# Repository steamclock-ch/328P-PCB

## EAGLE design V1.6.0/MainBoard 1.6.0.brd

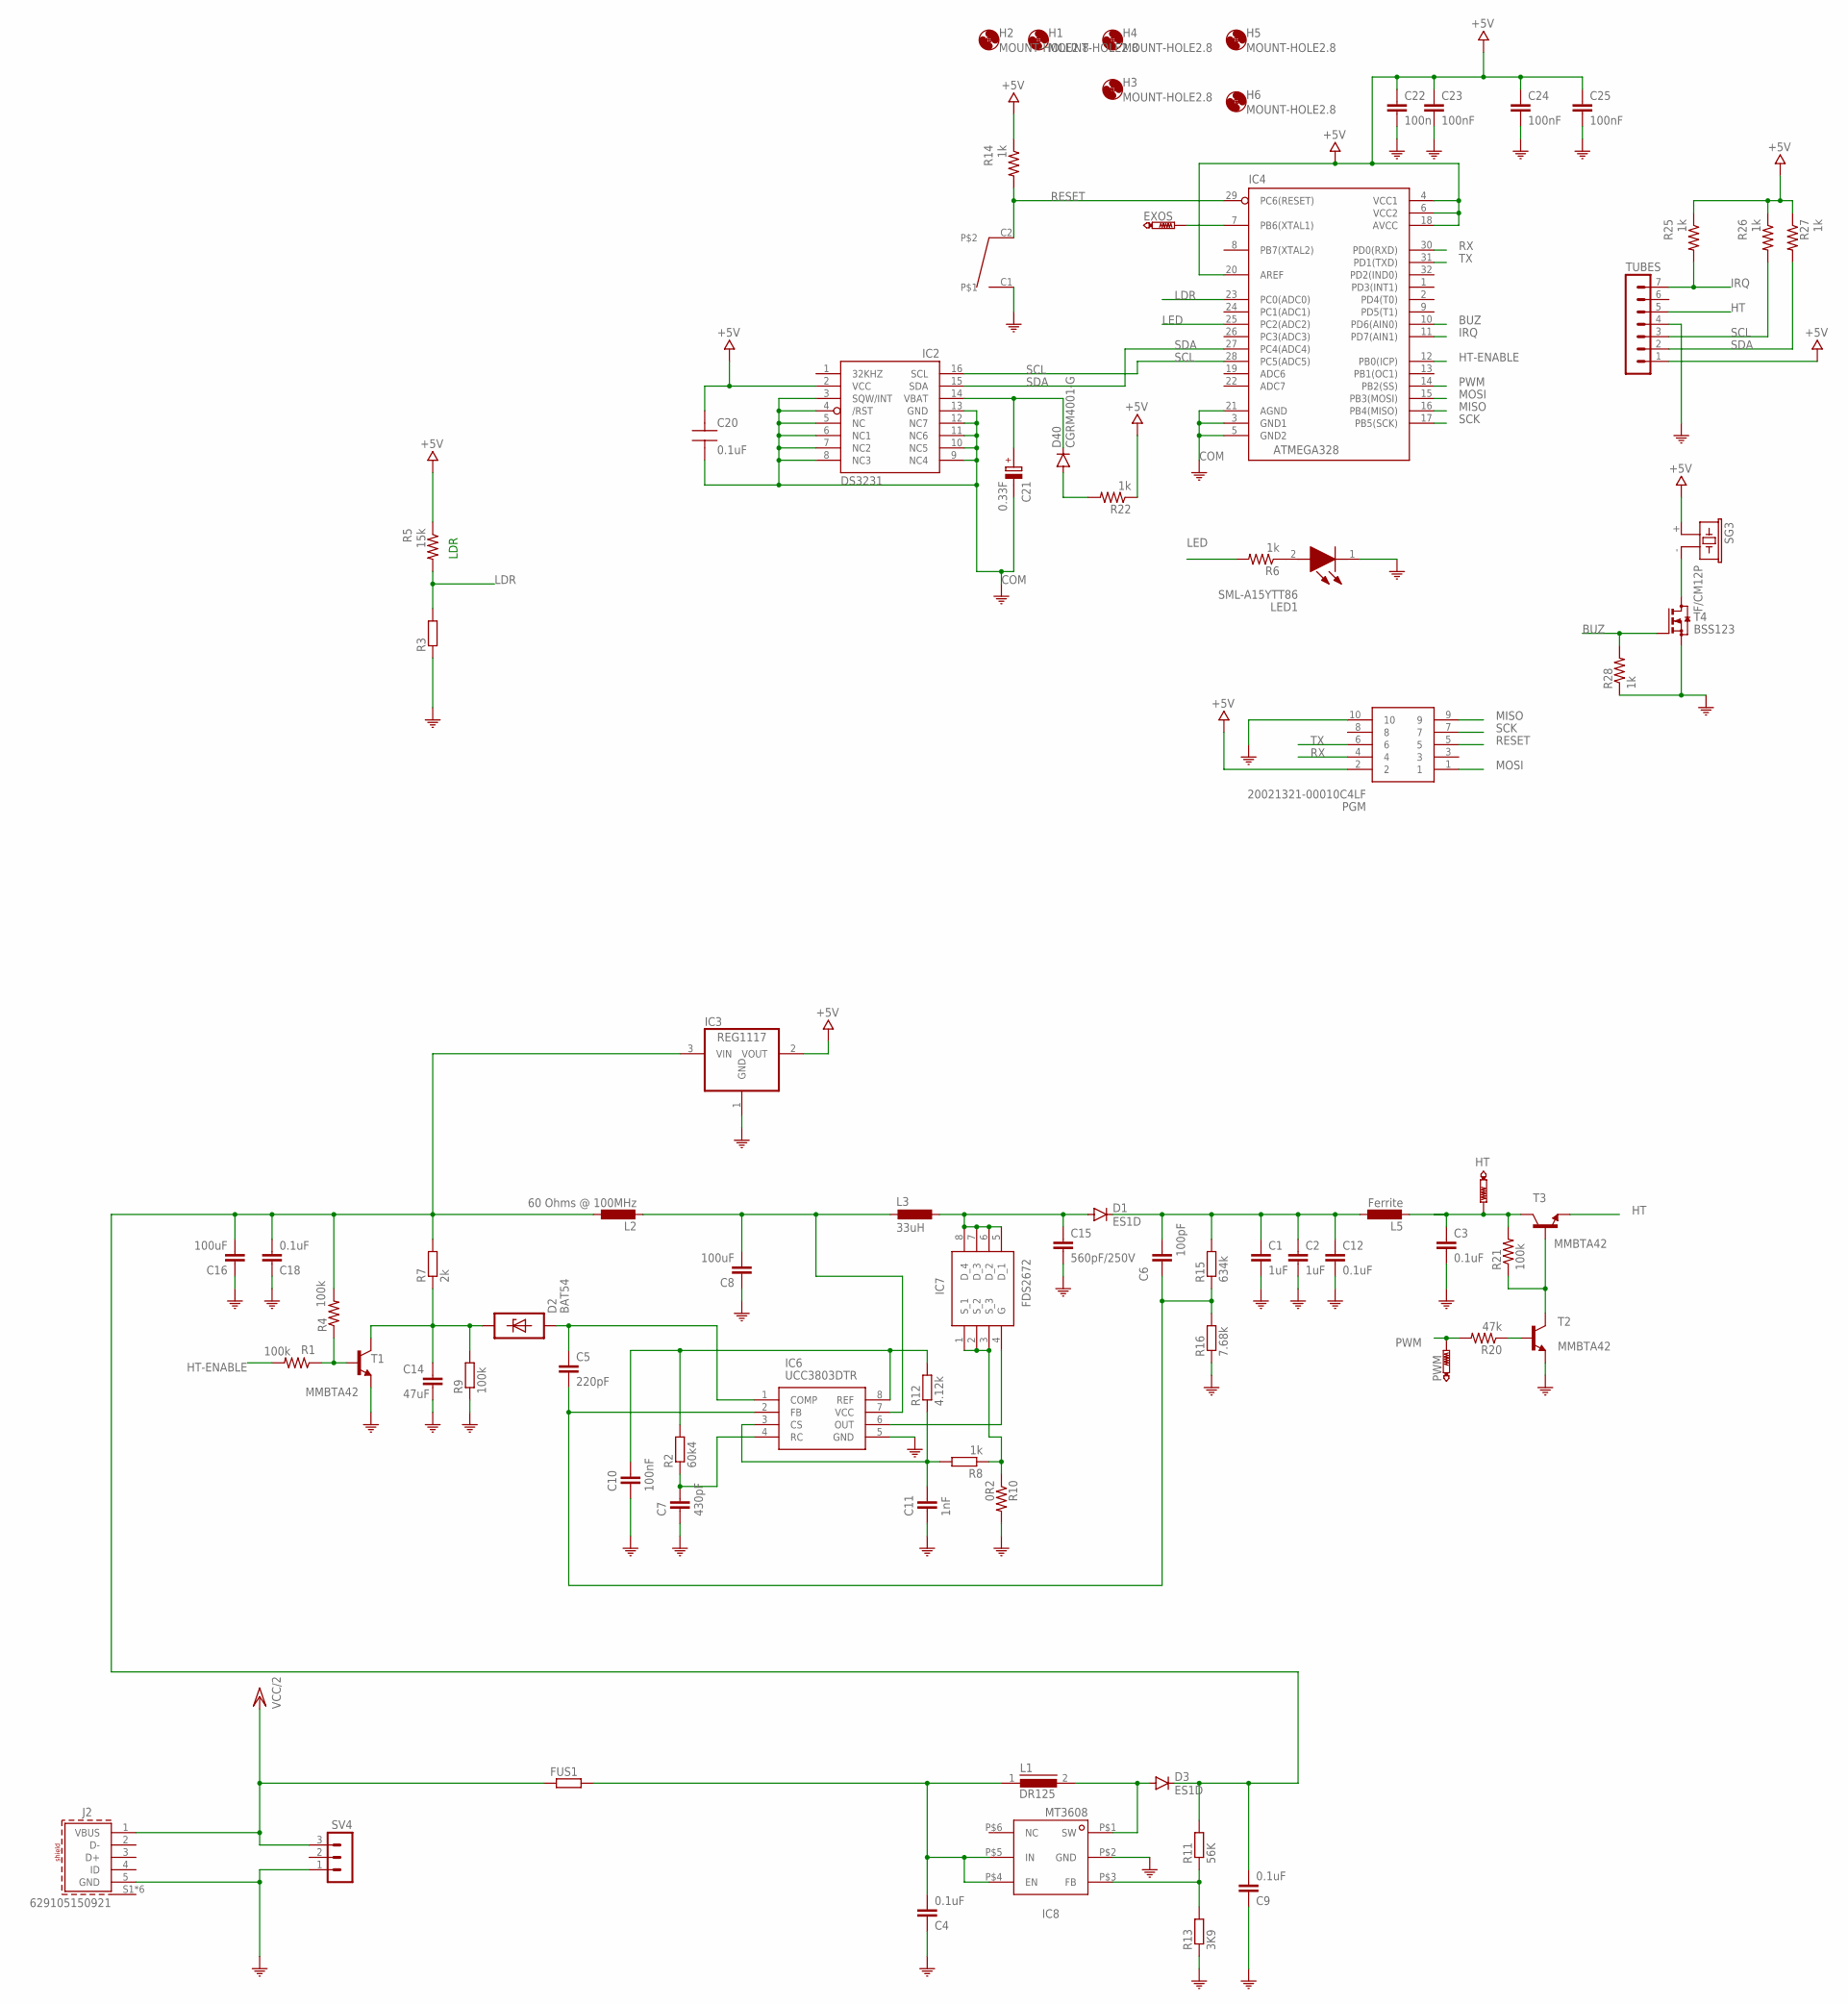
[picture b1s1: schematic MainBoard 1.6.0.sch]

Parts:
C1, C2: 1uF; C1812K; MOUSER 810-CGA8P3X7T2E105MA
C3, C12: 0.1uF; C1808; MOUSER 581-1808PC104KAT1A
C4: 0.1uF; C1206; MOUSER 963-LMF105B7104KVHF
C5: 220pF; C0402; MOUSER 963-LMK042B7221KC-W
C6: 100pF; C0805; MOUSER 81-GCM21A5C2E101JX1D
C7: 430pF; C0805; MOUSER 581-08055A431JAT4A
C8, C16: 100uF; C1210; MOUSER 963-EMK325ABJ107MM-P
C9: 0.1uF; C1206K; MOUSER 963-LMF105B7104KVHF
C10: 100nF; C0805; MOUSER 963-EMF212B7104KGHT
C11: 1nF; C0805; MOUSER 80-C0805C182G4HACTU
C14: 47uF; C1210; MOUSER 963-EMK325BJ476MM-P
C15: 560pF/250V; C0603; MOUSER 80-C0603C561JAG
C18: 0.1uF; C0402; MOUSER 963-LMF105B7104KVHF
C20: 0.1uF; CAP0805-NP
C21: 0.33F; ELNA21.5X8.0; MOUSER 555-DBN-5R5D334T
C22: 100n; C0603
C23, C24, C25: 100nF; C0603
D1, D3: ES1D; SMB; MOUSER 512-ES1DF
D2: BAT54; SOD323; MOUSER 621-BAT54WS-F
D40: CGRM4001-G; SOD-123_MINI-SMA; MOUSER 863-NSR0320MW2T1G
EXOS: PTR1TP09R; TP09R
FUS1: R-EU_R6332; R6332; MOUSER 530-0ZCG0150AF2C
H1, H2, H3, H4, H5, H6: MOUNT-HOLE2.8; 2,8
HT: PTR1TP09R; TP09R
IC2: DS3231/SO; SO16W; MOUSER 700-DS3231SN#
IC3: REG1117; SOT223
IC4: ATMEGA328; QFP032
IC6: UCC3803DTR; SOIC127P600X175-8N; MOUSER 595-UCC3803D
IC7: FDS2672; SOIC127P600X175-8N; MOUSER 512-FDS2672
IC8: MT3608SOT23-6; SOT23-6
J2: 629105150921; MOUSER 710-629105150921
L1: DR125
L2: 60 Ohms @ 100MHz; L2012C; MOUSER 963-BKP2125HS600-T
L3: 33uH; MSS7341; MOUSER 710-784770330
L5: Ferrite; L2012C; MOUSER 963-BKP2125HS600-T
LED1: SML-A15YTT86; SMLA15YTT86; MOUSER 755-SML-A15YTT86
PGM: 20021321-00010C4LF; 2002132100010C4LF
PWM: PTR1TP09R; TP09R
R1, R4, R9, R21: 100k; R0805
R2: 60k4; R0805; MOUSER 603-RT0805FRE0760K4L
R3: R-EU_0204/2V; 0204V
R5: 15k; M2012
R6, R14, R22, R25, R26, R27, R28: 1k; M2012
R7: 2k; R0805; MOUSER 754-RR1220P-202D
R8: 1k; R0805
R10: 0R2; R2010; MOUSER 603-PE2010FKE070R1L
R11: 56K; R0805; MOUSER 71-CRCW0603-634K-E3
R12: 4.12k; R0805; MOUSER 660-RN732ATD4121F100
R13: 3K9; R0805; MOUSER 71-CRCW0603-634K-E3
R15: 634k; R0805; MOUSER 71-CRCW0603-634K-E3
R16: 7.68k; R0805; MOUSER 71-CRCW0805-7.68K-E3
R20: 47k; R0805
SG3: F/CM12P
SV4: MA03-1
T1, T2, T3: MMBTA42; SOT23
T4: BSS123; SOT23; MOUSER 726-BSS123NH6433
TUBES: MA07-1
U$5: D-VERTSW; FP-VERTSW; MOUSER 612-TL6190BUTTON

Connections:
+5V: C20.1, C22.1, C23.1, C24.1, C25.1, IC2.2 (VCC), IC3.2 (VOUT), IC4.4 (VCC1), IC4.6 (VCC2), IC4.18 (AVCC), IC4.20 (AREF), PGM.2, R5.1, R14.1, R22.1, R25.1, R26.1, R27.1, SG3.+ (1), TUBES.1
BATT: C21.+, D40.C, IC2.14 (VBAT)
BUZ: IC4.10 (PD6(AIN0)), R28.2, T4.1 (G)
COM: C1.2, C2.2, C3.2, C4.2, C7.2, C8.1, C9.2, C10.2, C11.2, C12.2, C14.2, C15.2, C16.1, C18.2, C20.2, C21.-, C22.2, C23.2, C24.2, C25.2, IC2.3 (SQW/INT), IC2.4 (/RST), IC2.5 (NC), IC2.6 (NC1), IC2.7 (NC2), IC2.8 (NC3), IC2.9 (NC4), IC2.10 (NC5), IC2.11 (NC6), IC2.12 (NC7), IC2.13 (GND), IC3.1 (GND), IC4.3 (GND1), IC4.5 (GND2), IC4.21 (AGND), IC6.5 (GND), IC8.P$2 (GND), J2.5 (GND), LED1.1 (K), PGM.10, R3.1, R9.1, R10.2, R13.1, R16.1, R28.1, SV4.1, T1.2 (E), T2.2 (E), T4.2 (S), TUBES.4, U$5.C1
CS: C11.1, IC6.3 (CS), R8.2, R12.1
FB: C5.2, C6.2, IC6.2 (FB), R15.1, R16.2
HT: T3.2 (E), TUBES.5
HT-ENABLE: IC4.12 (PB0(ICP)), R1.2
IRQ: IC4.11 (PD7(AIN1)), R25.2, TUBES.7
LDR: IC4.23 (PC0(ADC0)), R3.2, R5.2
LED: IC4.25 (PC2(ADC2)), R6.2
MISO: IC4.16 (PB4(MISO)), PGM.9
MOSI: IC4.15 (PB3(MOSI)), PGM.1
unnamed: LED1.2 (A), R6.1
unnamed: C4.1, FUS1.2, IC8.P$4 (EN), IC8.P$5 (IN), L1.1
unnamed: SG3.- (2), T4.3 (D)
unnamed: EXOS.TP, IC4.7 (PB6(XTAL1))
unnamed: C1.1, C2.1, C6.1, C12.1, D1.C, L5.1, R15.2
unnamed: R21.1, T2.3 (C), T3.1 (B)
unnamed: R1.1, R4.1, T1.1 (B)
unnamed: C14.1, D2.C (1), R7.1, R9.2, T1.3 (C)
unnamed: C5.1, D2.A (2), IC6.1 (COMP)
unnamed: IC8.P$3 (FB), R11.1, R13.2
unnamed: IC7.1 (S_1), IC7.2 (S_2), IC7.3 (S_3), R8.1, R10.1
unnamed: D3.A, IC8.P$1 (SW), L1.2
unnamed: C8.2, IC6.7 (VCC), L2.2, L3.1
unnamed: C15.1, D1.A, IC7.5 (D_1), IC7.6 (D_2), IC7.7 (D_3), IC7.8 (D_4), L3.2
unnamed: R20.1, T2.1 (B)
unnamed: D40.A, R22.2
OUT: IC6.6 (OUT), IC7.4 (G)
POSTFUSE: C9.1, C16.2, C18.1, D3.C, IC3.3 (VIN), L2.1, R4.2, R7.2, R11.2
PWM: IC4.14 (PB2(SS)), PWM.TP, R20.2
RAW_HT: C3.1, HT.TP, L5.2, R21.2, T3.3 (C)
RC: C7.1, IC6.4 (RC), R2.1
REF: C10.1, IC6.8 (REF), R2.2, R12.2
RESET: IC4.29 (PC6(RESET)), PGM.5, R14.2, U$5.C2
RX: IC4.30 (PD0(RXD)), PGM.4
SCK: IC4.17 (PB5(SCK)), PGM.7
SCL: IC2.16 (SCL), IC4.28 (PC5(ADC5)), R26.2, TUBES.3
SDA: IC2.15 (SDA), IC4.27 (PC4(ADC4)), R27.2, TUBES.2
TX: IC4.31 (PD1(TXD)), PGM.6
VCC/2: FUS1.1, J2.1 (VBUS), SV4.3

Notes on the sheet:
LDR

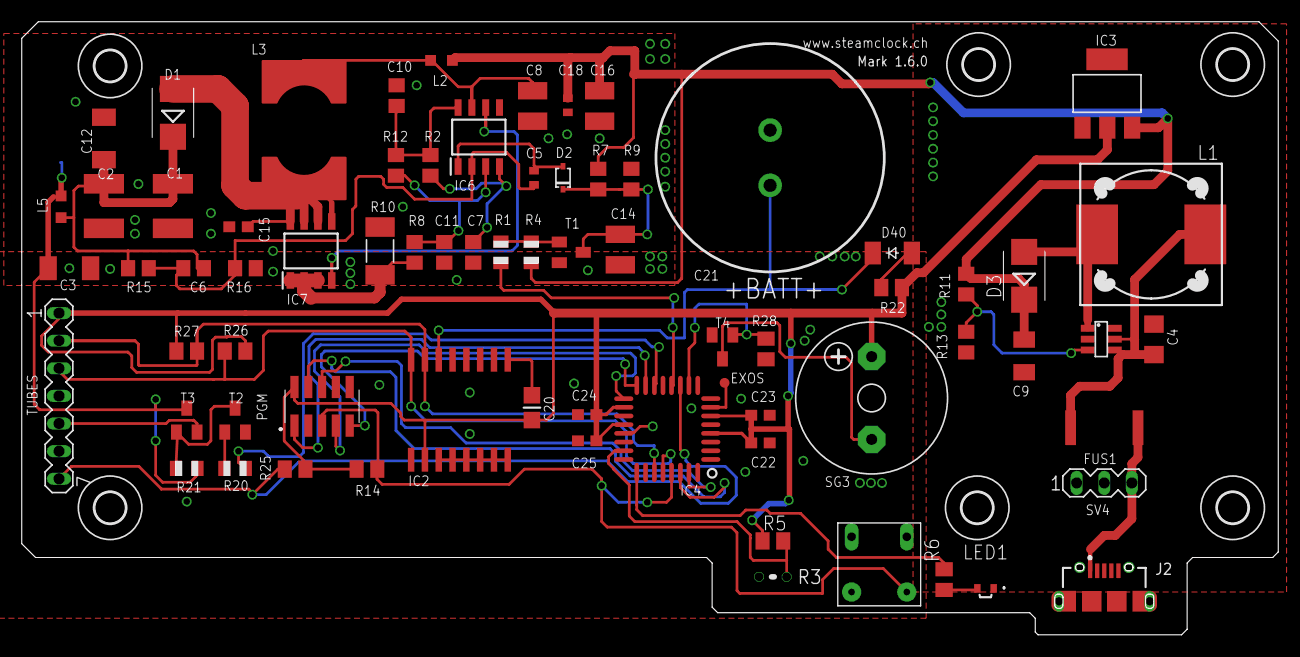
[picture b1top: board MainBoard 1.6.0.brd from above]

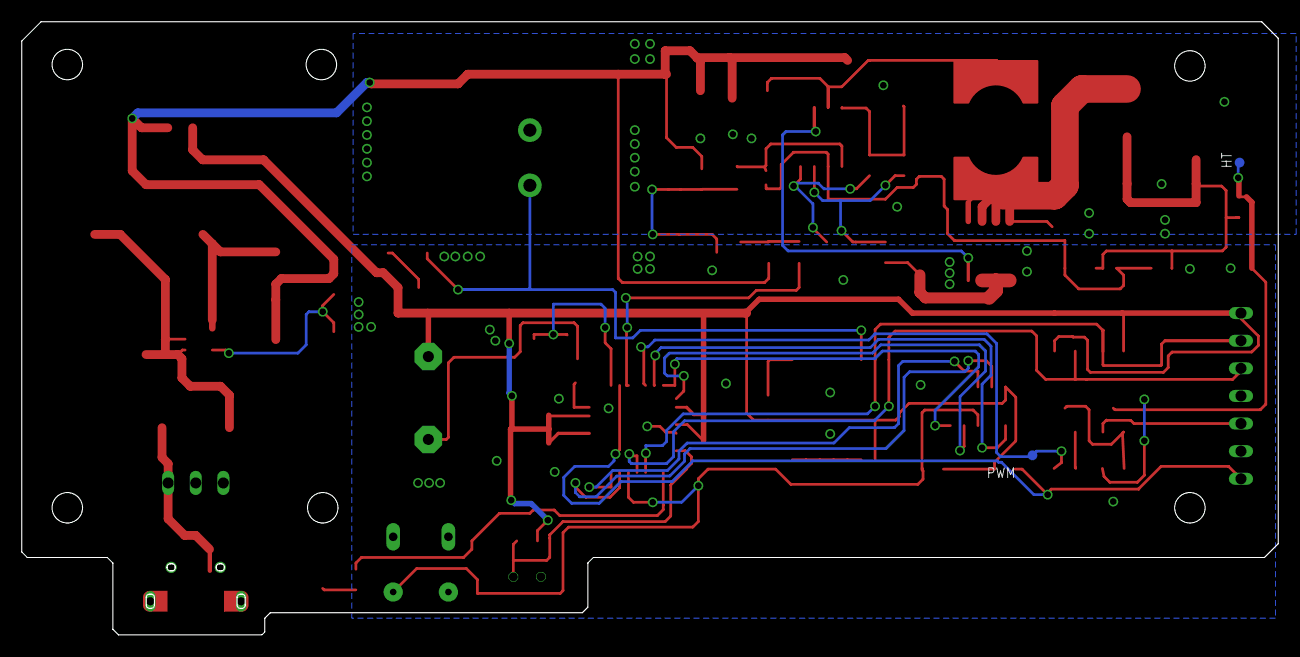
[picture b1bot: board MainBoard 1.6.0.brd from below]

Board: 2 copper layers, 115.5 x 56.3 mm, 80 parts (2 on the bottom side), 42 nets.

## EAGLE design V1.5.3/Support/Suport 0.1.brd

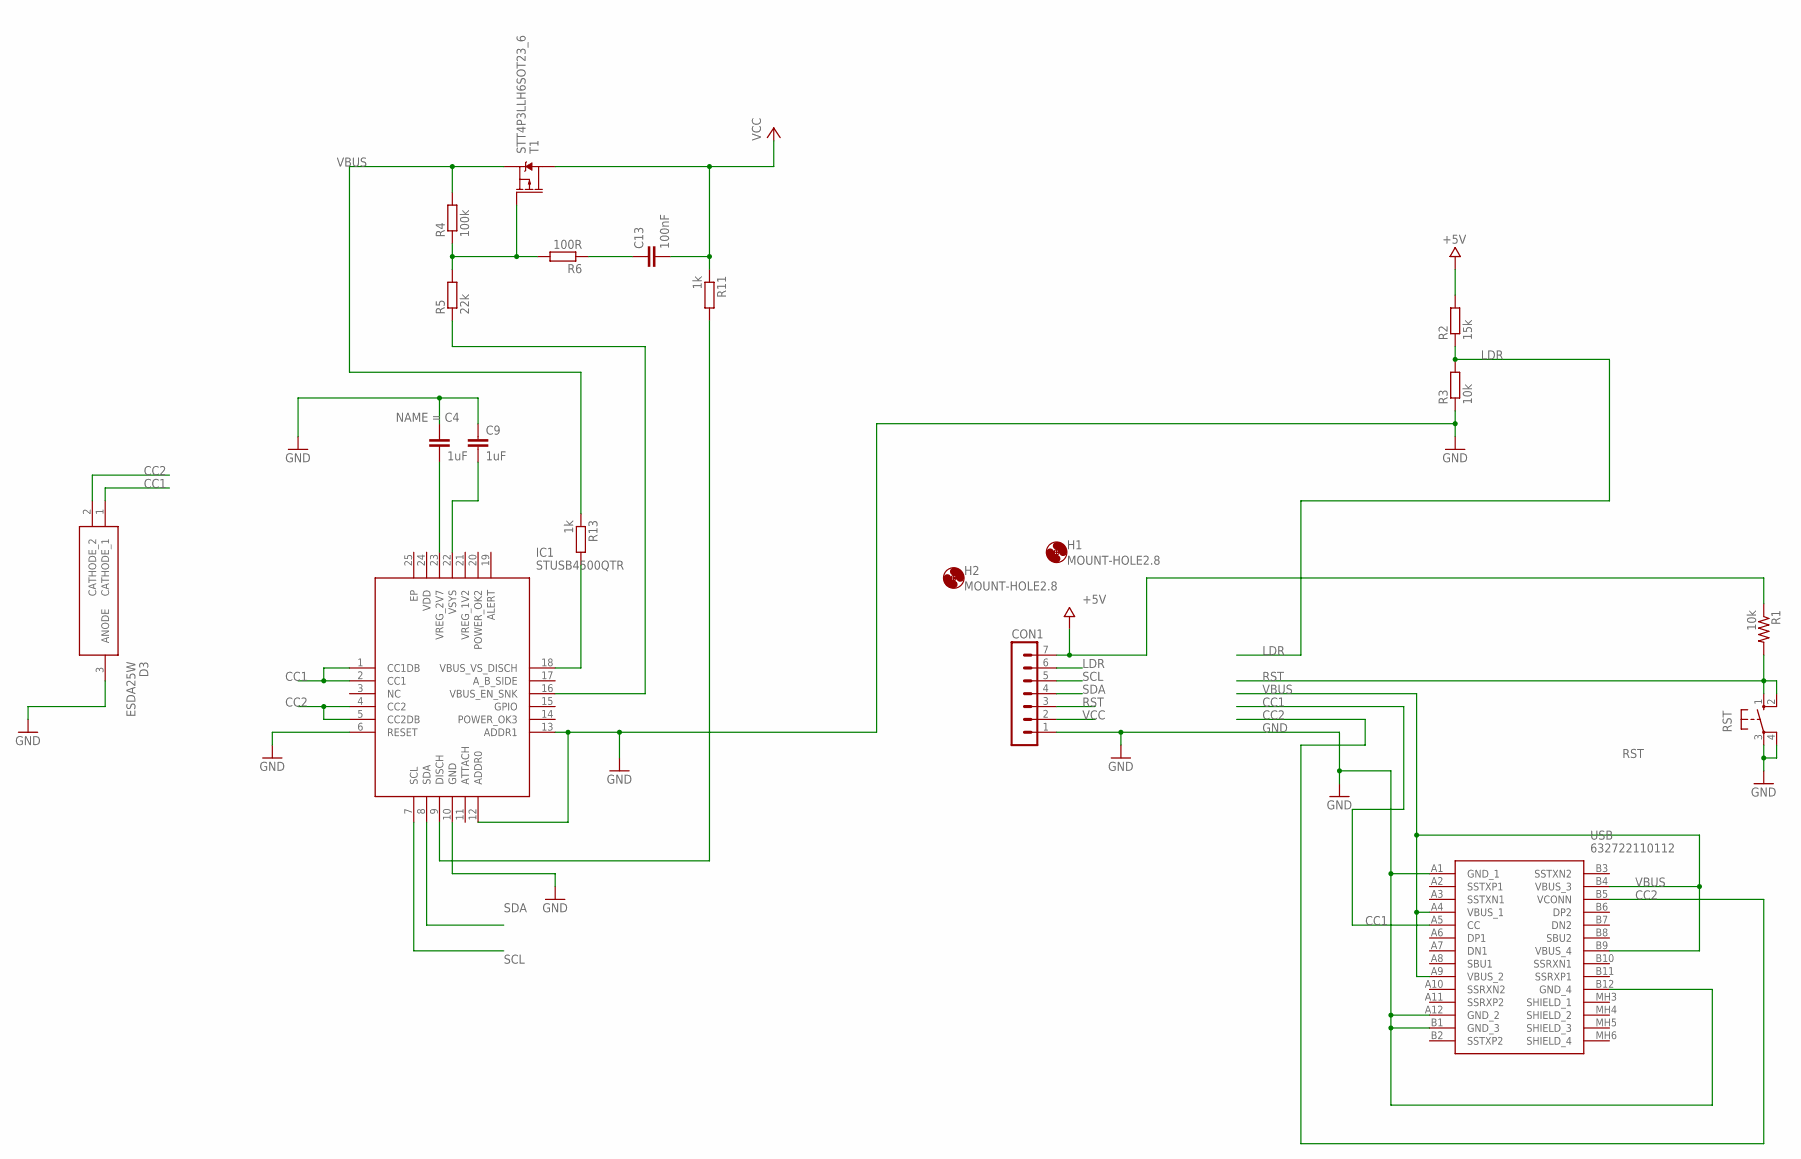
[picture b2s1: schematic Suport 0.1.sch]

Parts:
C4: 1uF; C0603; MOUSER_PART_NUMBER 81-GRM155R61E105KA2D
C9: 1uF; C0603
C13: 100nF; C0402; MOUSER_PART_NUMBER 710-885012205050
CON1: MA07-1
D3: ESDA25W; SOT65P210X110-3N
H1, H2: MOUNT-HOLE2.8; 2,8
IC1: STUSB4500QTR; QFN50P400X400X100-25N
R1, R3: 10k; M2012
R2: 15k; 0204V
R4: 100k; R0805
R5: 22k; R0805
R6: 100R; R0805
R11, R13: 1k; R0805
RST: 10-XX; B3F-10XX
T1: STT4P3LLH6SOT23_6; SOT23-6
USB: 632722110112

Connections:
+5V: CON1.7, R1.1, R2.2
CC1: D3.1 (CATHODE_1), IC1.1 (CC1DB), IC1.2 (CC1), USB.A5 (CC)
CC2: D3.2 (CATHODE_2), IC1.4 (CC2), IC1.5 (CC2DB), USB.B5 (VCONN)
GND: C4.1, C9.1, CON1.1, D3.3 (ANODE), IC1.6 (RESET), IC1.10 (GND), IC1.12 (ADDR0), IC1.13 (ADDR1), R3.1, RST.3, RST.4 (P1), USB.A1 (GND_1), USB.A12 (GND_2), USB.B1 (GND_3), USB.B12 (GND_4)
LDR: CON1.6, R2.1, R3.2
unnamed: C4.2, IC1.23 (VREG_2V7)
unnamed: C9.2, IC1.22 (VSYS)
unnamed: R4.1, R5.2, R6.2, T1.3 (G)
unnamed: C13.1, R6.1
unnamed: IC1.16 (VBUS_EN_SNK), R5.1
unnamed: IC1.9 (DISCH), R11.2
unnamed: IC1.18 (VBUS_VS_DISCH), R13.2
RST: CON1.3, R1.2, RST.1 (S), RST.2 (S1)
SCL: CON1.5, IC1.7 (SCL)
SDA: CON1.4, IC1.8 (SDA)
VBUS: R4.2, R13.1, T1.4 (S), USB.A4 (VBUS_1), USB.A9 (VBUS_2), USB.B4 (VBUS_3), USB.B9 (VBUS_4)
VCC: C13.2, CON1.2, R11.1, T1.1 (D), T1.2 (D), T1.5 (D), T1.6 (D)

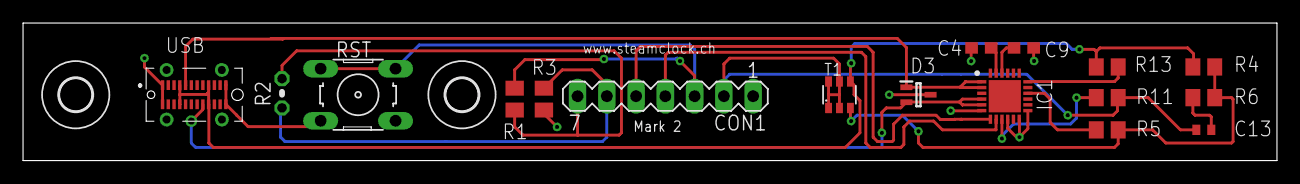
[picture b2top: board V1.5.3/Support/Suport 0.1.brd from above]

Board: 2 copper layers, 108.8 x 11.9 mm, 19 parts (0 on the bottom side), 17 nets.

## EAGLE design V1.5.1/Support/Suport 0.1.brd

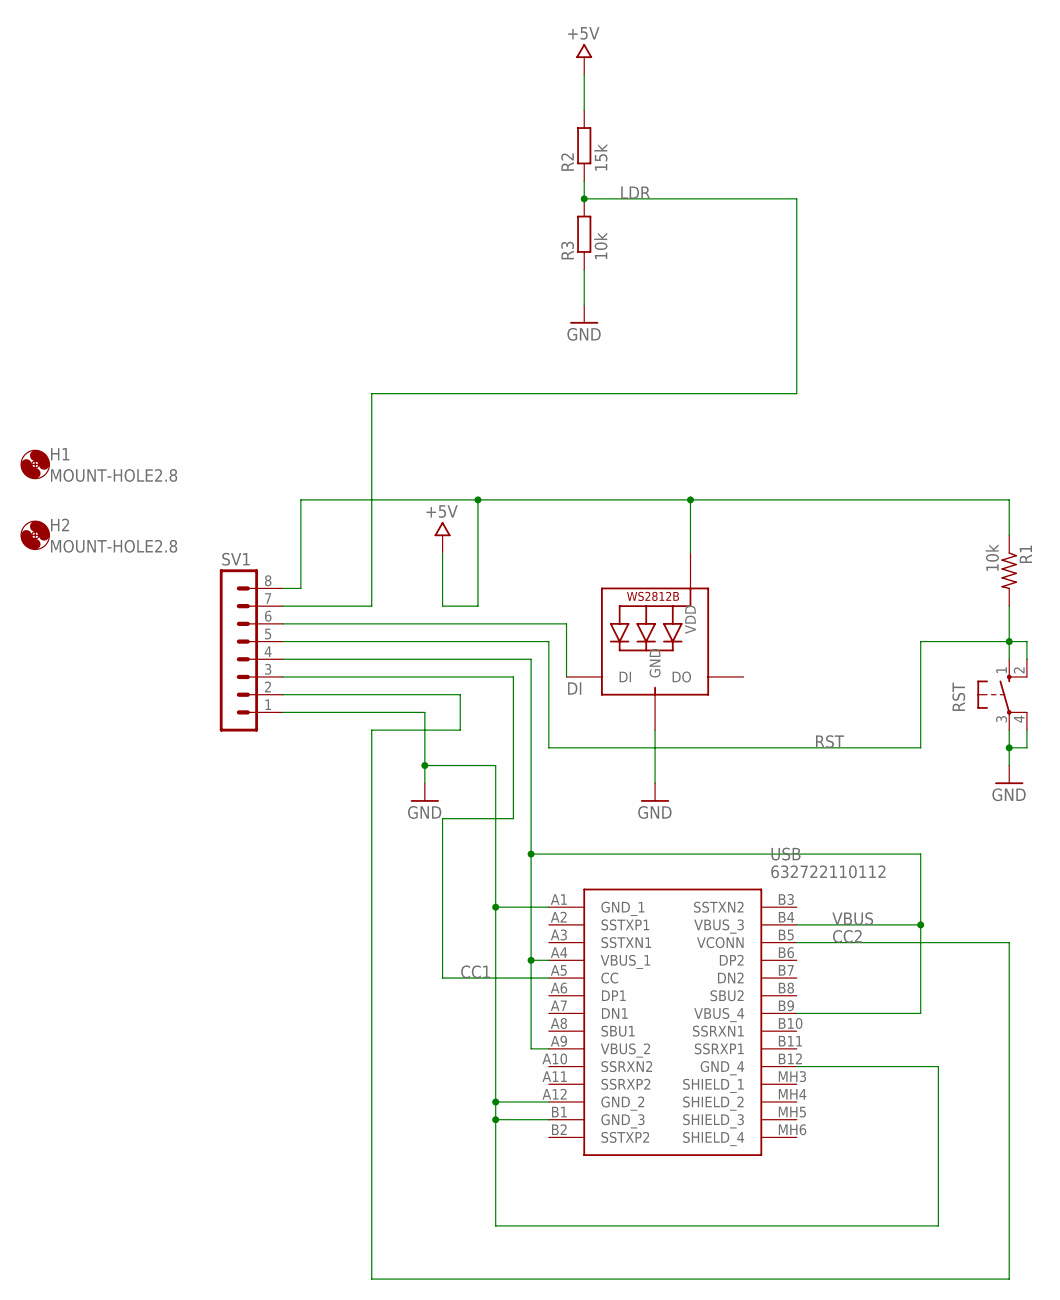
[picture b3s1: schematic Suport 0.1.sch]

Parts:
H1, H2: MOUNT-HOLE2.8; 2,8
LED1: WS2812B3535; LED3535
R1, R3: 10k; M2012
R2: 15k; 0204V
RST: 10-XX; B3F-10XX
SV1: MA08-1
USB: 632722110112

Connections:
+5V: LED1.2 (VDD), R1.1, R2.2, SV1.8
CC1: SV1.3, USB.A5 (CC)
CC2: SV1.2, USB.B5 (VCONN)
DI: LED1.1 (DI), SV1.6
GND: LED1.4 (GND), R3.1, RST.3, RST.4 (P1), SV1.1, USB.A1 (GND_1), USB.A12 (GND_2), USB.B1 (GND_3), USB.B12 (GND_4)
LDR: R2.1, R3.2, SV1.7
RST: R1.2, RST.1 (S), RST.2 (S1), SV1.5
VBUS: SV1.4, USB.A4 (VBUS_1), USB.A9 (VBUS_2), USB.B4 (VBUS_3), USB.B9 (VBUS_4)

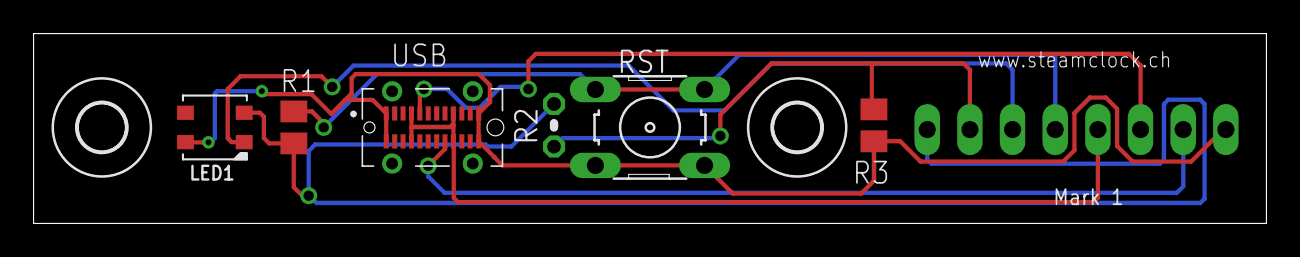
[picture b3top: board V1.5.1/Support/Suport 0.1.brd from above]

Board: 2 copper layers, 73.4 x 11.3 mm, 9 parts (1 on the bottom side), 8 nets.

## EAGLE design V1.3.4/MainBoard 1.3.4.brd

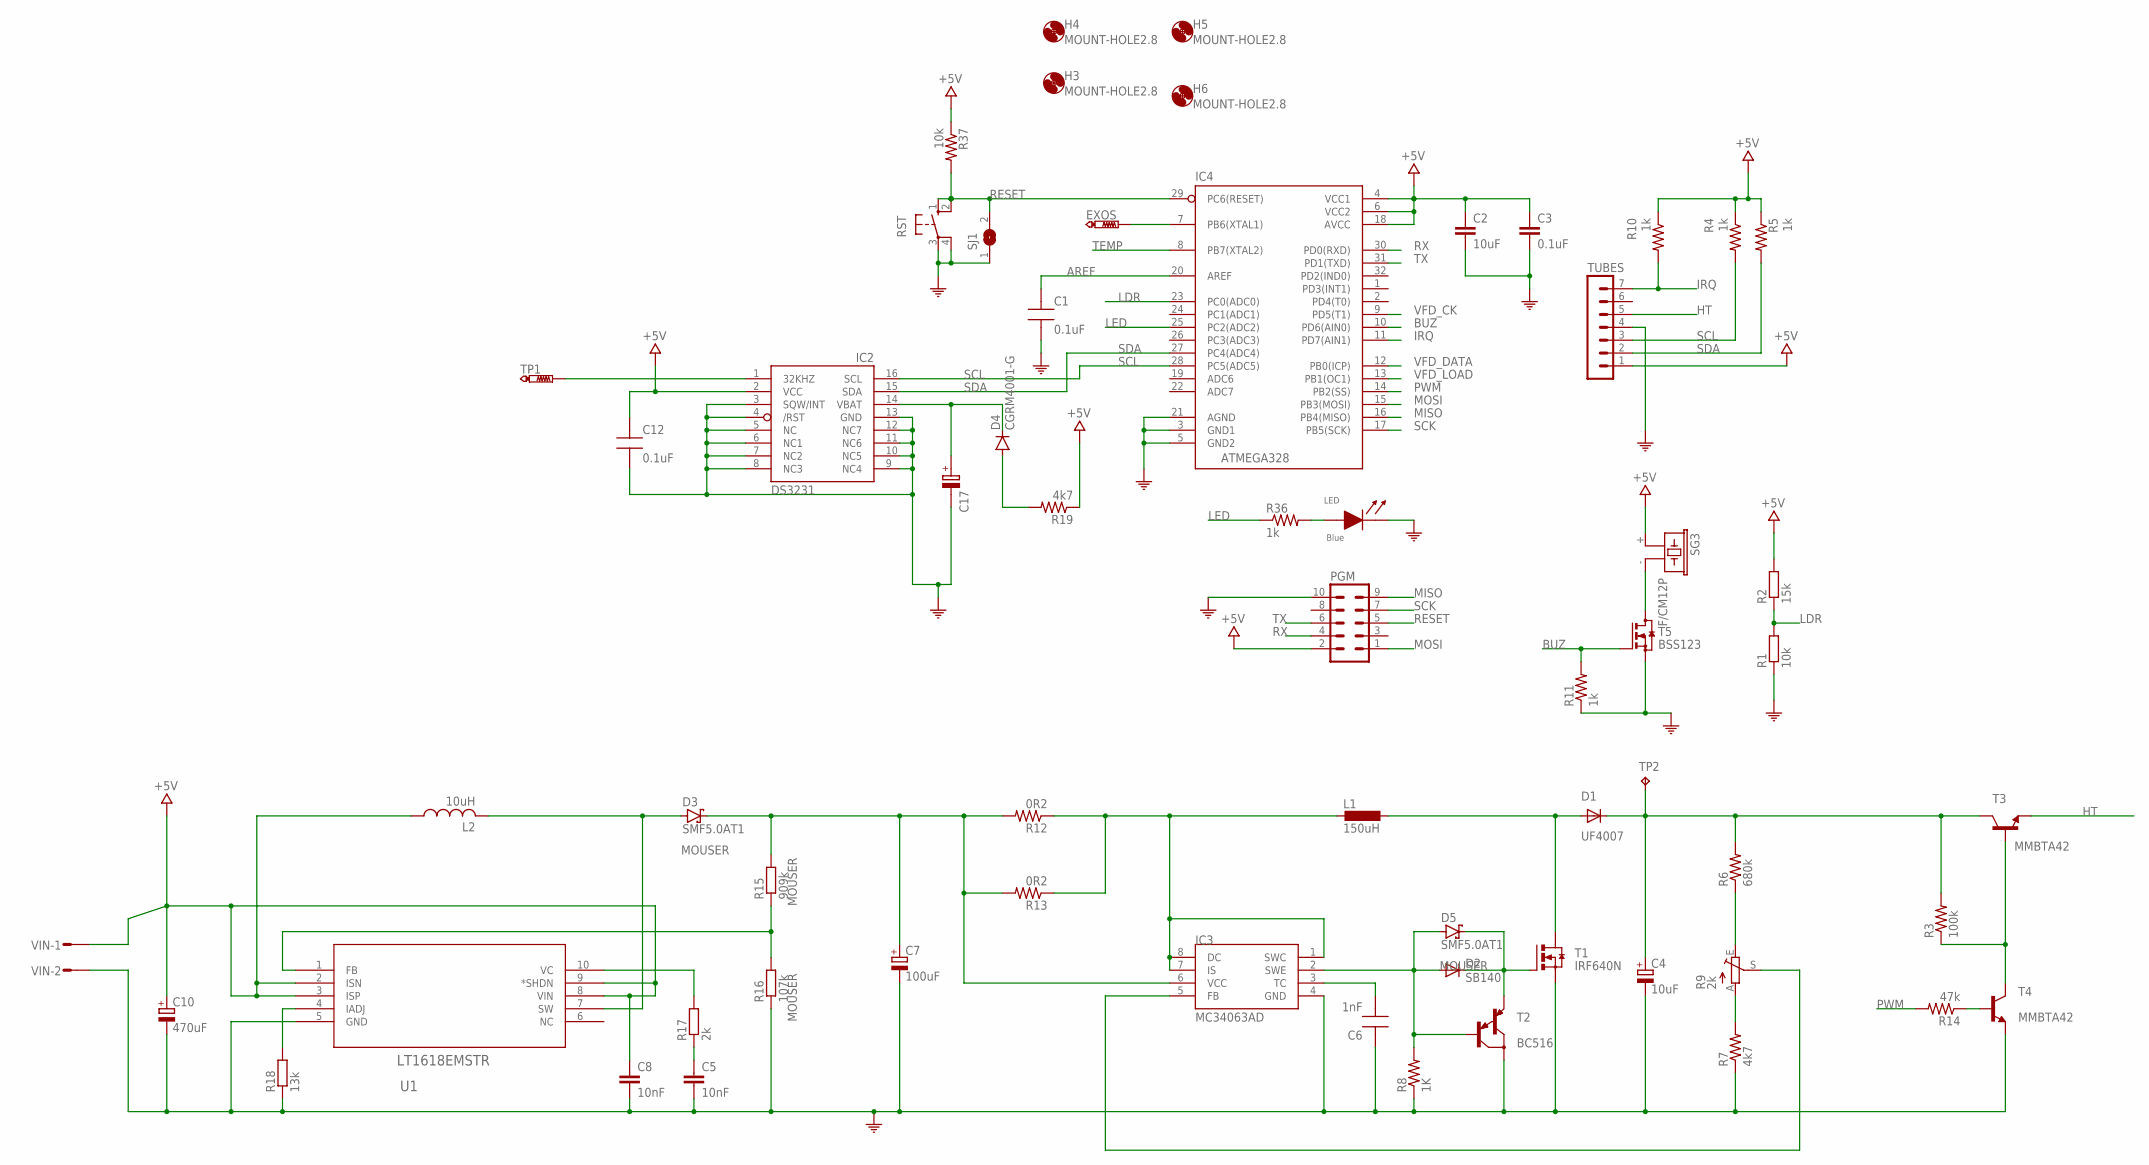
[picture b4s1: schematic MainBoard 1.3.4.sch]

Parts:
C1, C12: 0.1uF; CAP0805-NP
C2: 10uF; C0603; MOUSER 791-0603X106K100CT
C3: 0.1uF; C0402K; MOUSER 963-JMK042BJ104KC-W
C4: 10uF; E3,5-10
C5, C8: 10nF; C0805
C6: 1nF; CAP0805-NP
C7: 100uF; E2,5-6E
C10: 470uF; 153CLV-0810; MOUSER 710-865080253012
C17: AHG-35/100-RADIAL; ELNA21.5X8.0; MOUSER 555-DB-5R5D474T
D1: UF4007; F126-10
D2: SB140; DO07
D3, D5: SMF5.0AT1; SOD123FL; MOUSER 863-MBR0520LT1G
D4: CGRM4001-G; SOD-123_MINI-SMA; MOUSER 863-NSR0320MW2T1G
EXOS: PTR1TP09R; TP09R
H3, H4, H5, H6: MOUNT-HOLE2.8; 2,8
IC2: DS3231/SO; SO16W
IC3: MC34063AD; SOIC8
IC4: ATMEGA328; QFP032
L1: 150uH; DO3316P
L2: 10uH; L5650M; MOUSER 851-CR43NP-100MC
LED: Blue; LED0805
PGM: MA05-2
R1, R37: 10k; M2012
R2: 15k; 0204V
R3: 100k; R2012
R4, R5, R10, R11, R36: 1k; M2012
R6: 680k; R2012
R7: 4k7; R2012
R8: 1K; R2012
R9: 2k; B25P
R12, R13: 0R2; R2010
R14: 47k; R2012
R15: 909k; R0805; MOUSER 754-RR1220P-9093D-M
R16: 107k; R0805; MOUSER RR0816P-1073-D-04D
R17: 2k; R0805
R18: 13k; R0805
R19: 4k7; M2012
RST: 10-XX; B3F-10XX
SG3: F/CM12P
SJ1: SJW
T1: IRF640N; D2PACK
T2: BC516; TO92
T3, T4: MMBTA42; SOT23
T5: BSS123; SOT23
TP1: PTR1TP09R; TP09R
TP2: TPTP12R; TP12R
TUBES: MA07-1
U1: LT1618EMSTR; MSOP-10_MS; MOUSER 584-LT1618EMS#PBF
VIN: M02S; 02P

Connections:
+5V: C2.1, C3.1, C8.1, C10.+, C12.1, IC2.2 (VCC), IC4.4 (VCC1), IC4.6 (VCC2), IC4.18 (AVCC), L2.1, PGM.2, R2.2, R4.1, R5.1, R10.1, R19.1, R37.1, SG3.+ (1), TUBES.1, U1.2 (ISN), U1.3 (ISP), U1.8 (VIN), U1.9 (*SHDN), VIN.1
AREF: C1.1, IC4.20 (AREF)
BATT: C17.+, D4.C, IC2.14 (VBAT)
BUZ: IC4.10 (PD6(AIN0)), R11.2, T5.1 (G)
GND: C1.2, C2.2, C3.2, C4.-, C5.2, C6.1, C7.-, C8.2, C10.-, C12.2, C17.-, IC2.3 (SQW/INT), IC2.4 (/RST), IC2.5 (NC), IC2.6 (NC1), IC2.7 (NC2), IC2.8 (NC3), IC2.9 (NC4), IC2.10 (NC5), IC2.11 (NC6), IC2.12 (NC7), IC2.13 (GND), IC3.4 (GND), IC4.3 (GND1), IC4.5 (GND2), IC4.21 (AGND), LED.1 (CA), PGM.10, R1.1, R7.1, R8.1, R11.1, R16.1, R18.1, RST.3, RST.4 (P1), SJ1.1, T1.3 (S), T2.3 (C), T4.2 (E), T5.2 (S), TUBES.4, U1.5 (GND), VIN.2
HT: T3.2 (E), TUBES.5
IRQ: IC4.11 (PD7(AIN1)), R10.2, TUBES.7
LDR: IC4.23 (PC0(ADC0)), R1.2, R2.1
LED: IC4.25 (PC2(ADC2)), R36.1
MISO: IC4.16 (PB4(MISO)), PGM.9
MOSI: IC4.15 (PB3(MOSI)), PGM.1
unnamed: IC2.1 (32KHZ), TP1.TP
unnamed: D1.A, L1.2, T1.2 (D)
unnamed: SG3.- (2), T5.3 (D)
unnamed: EXOS.TP, IC4.7 (PB6(XTAL1))
unnamed: C6.2, IC3.3 (TC)
unnamed: R3.1, T3.1 (B), T4.3 (C)
unnamed: R7.2, R9.A
unnamed: D2.A, D5.A, IC3.2 (SWE), R8.2, T2.2 (B)
unnamed: R6.1, R9.E
unnamed: D3.A, L2.2, U1.7 (SW)
unnamed: R18.2, U1.4 (IADJ)
unnamed: LED.2 (AN), R36.2
unnamed: IC3.5 (FB), R9.S
unnamed: IC3.1 (SWC), IC3.7 (IS), IC3.8 (DC), L1.1, R12.1, R13.1
unnamed: R17.2, U1.10 (VC)
unnamed: R14.1, T4.1 (B)
unnamed: D2.C, D5.C, T1.1 (G), T2.1 (E)
unnamed: C5.1, R17.1
unnamed: D4.A, R19.2
unnamed: R15.1, R16.2, U1.1 (FB)
PWM: IC4.14 (PB2(SS)), R14.2
PWR: C7.+, D3.C, IC3.6 (VCC), R12.2, R13.2, R15.2
RAW_HT: C4.+, D1.C, R3.2, R6.2, T3.3 (C), TP2.TP
RESET: IC4.29 (PC6(RESET)), PGM.5, R37.2, RST.1 (S), RST.2 (S1), SJ1.2
RX: IC4.30 (PD0(RXD)), PGM.4
SCK: IC4.17 (PB5(SCK)), PGM.7
SCL: IC2.16 (SCL), IC4.28 (PC5(ADC5)), R4.2, TUBES.3
SDA: IC2.15 (SDA), IC4.27 (PC4(ADC4)), R5.2, TUBES.2
TEMP: IC4.8 (PB7(XTAL2))
TX: IC4.31 (PD1(TXD)), PGM.6
VFD_CK: IC4.9 (PD5(T1))
VFD_DATA: IC4.12 (PB0(ICP))
VFD_LOAD: IC4.13 (PB1(OC1))

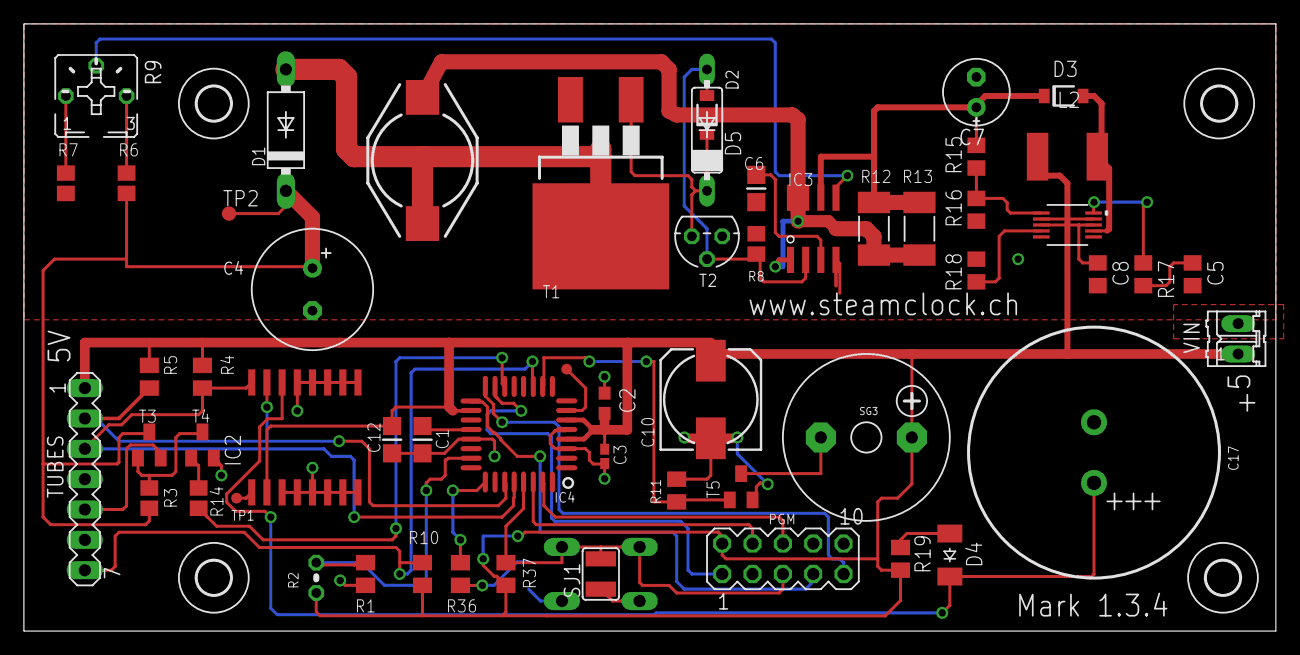
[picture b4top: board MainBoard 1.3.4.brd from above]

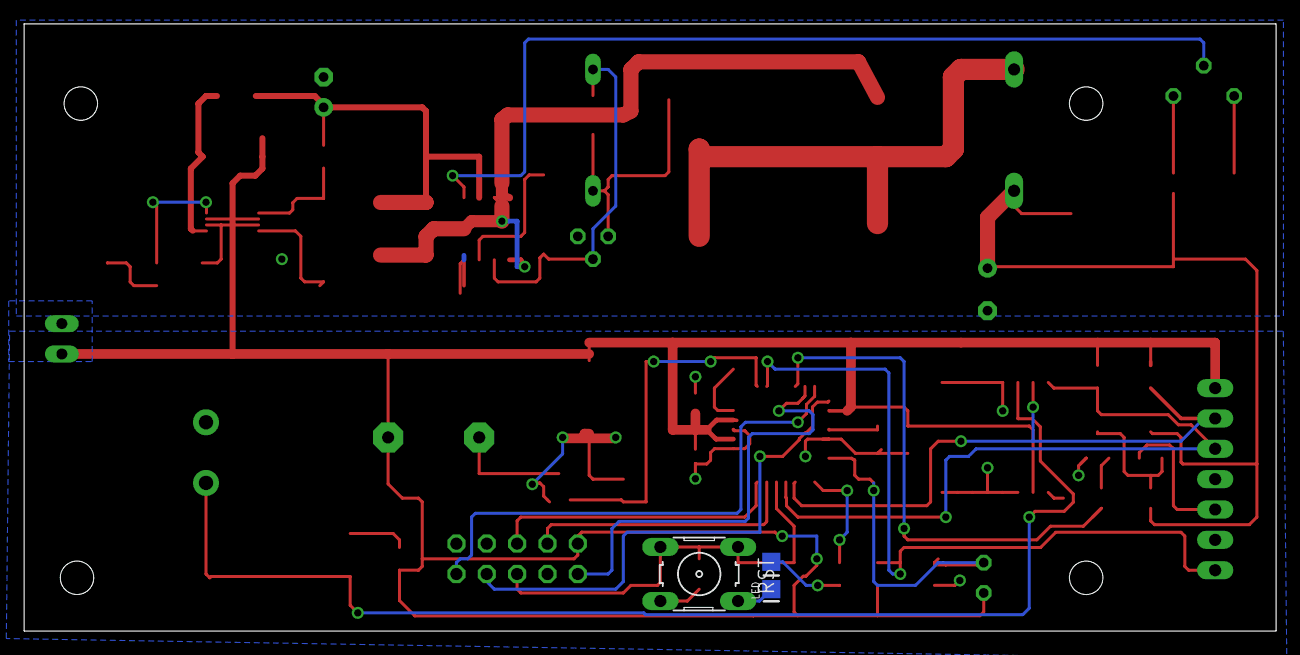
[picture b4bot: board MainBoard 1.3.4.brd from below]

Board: 2 copper layers, 104.8 x 50.8 mm, 62 parts (2 on the bottom side), 40 nets.

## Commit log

2022-07-02 init
2022-07-02 cleanup
2022-07-02 deleted backup versions
2022-07-02 clean up older files than 1.9.2

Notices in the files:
parts and their libraries:
Wurth_Connectors_WR-USB: Copyright: Würth Elektronik
